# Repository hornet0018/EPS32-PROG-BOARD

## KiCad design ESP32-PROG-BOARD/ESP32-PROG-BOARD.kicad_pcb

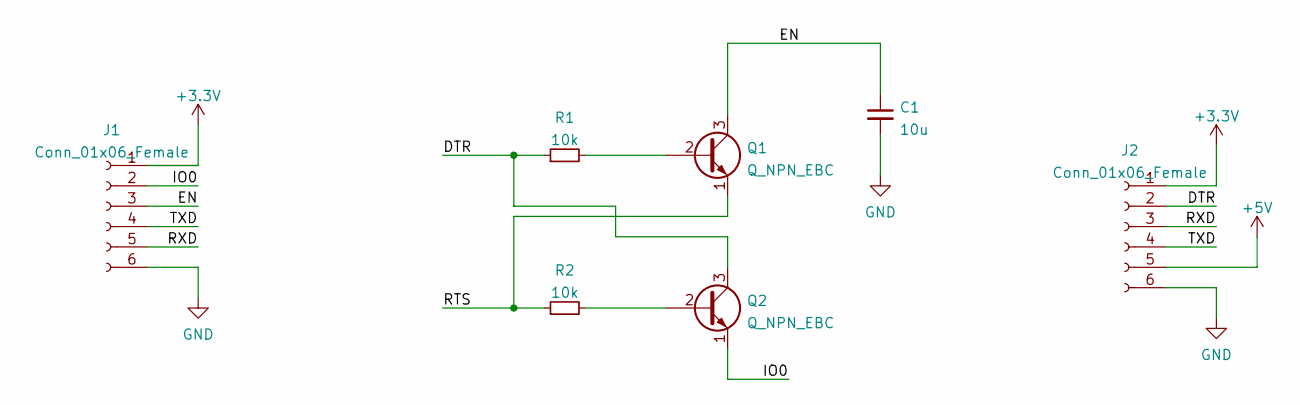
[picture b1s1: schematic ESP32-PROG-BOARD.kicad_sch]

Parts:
C1: 10u; C_0603_1608Metric_Pad1.08x0.95mm_HandSolder
J1: Conn_01x06_Female; PinSocket_1x07_P2.00mm_Horizontal
J2: Conn_01x06_Female; PinSocket_1x06_P2.54mm_Vertical
Q1, Q2: Q_NPN_EBC; TO-92
R1, R2: 10k; R_0603_1608Metric_Pad0.98x0.95mm_HandSolder

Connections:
+3V3: J1.1, J2.1
+5V: J2.5
/DTR: J2.2, Q2.3 (C), R1.1
/EN: C1.1, J1.3, Q1.3 (C)
/IO0: J1.2, Q2.1 (E)
/RTS: Q1.1 (E), R2.1
/RXD: J1.5, J2.3
/TXD: J1.4, J2.4
GND: C1.2, J1.6, J2.6
unnamed: Q1.2 (B), R1.2
unnamed: Q2.2 (B), R2.2

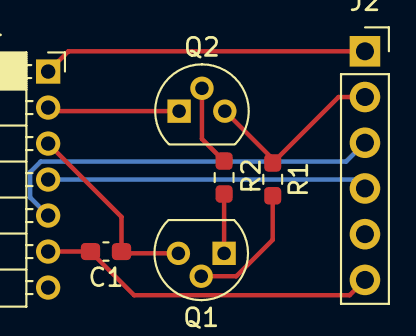
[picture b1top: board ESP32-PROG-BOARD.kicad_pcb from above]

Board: 2 copper layers, 7 parts (0 on the bottom side), 10 nets.
